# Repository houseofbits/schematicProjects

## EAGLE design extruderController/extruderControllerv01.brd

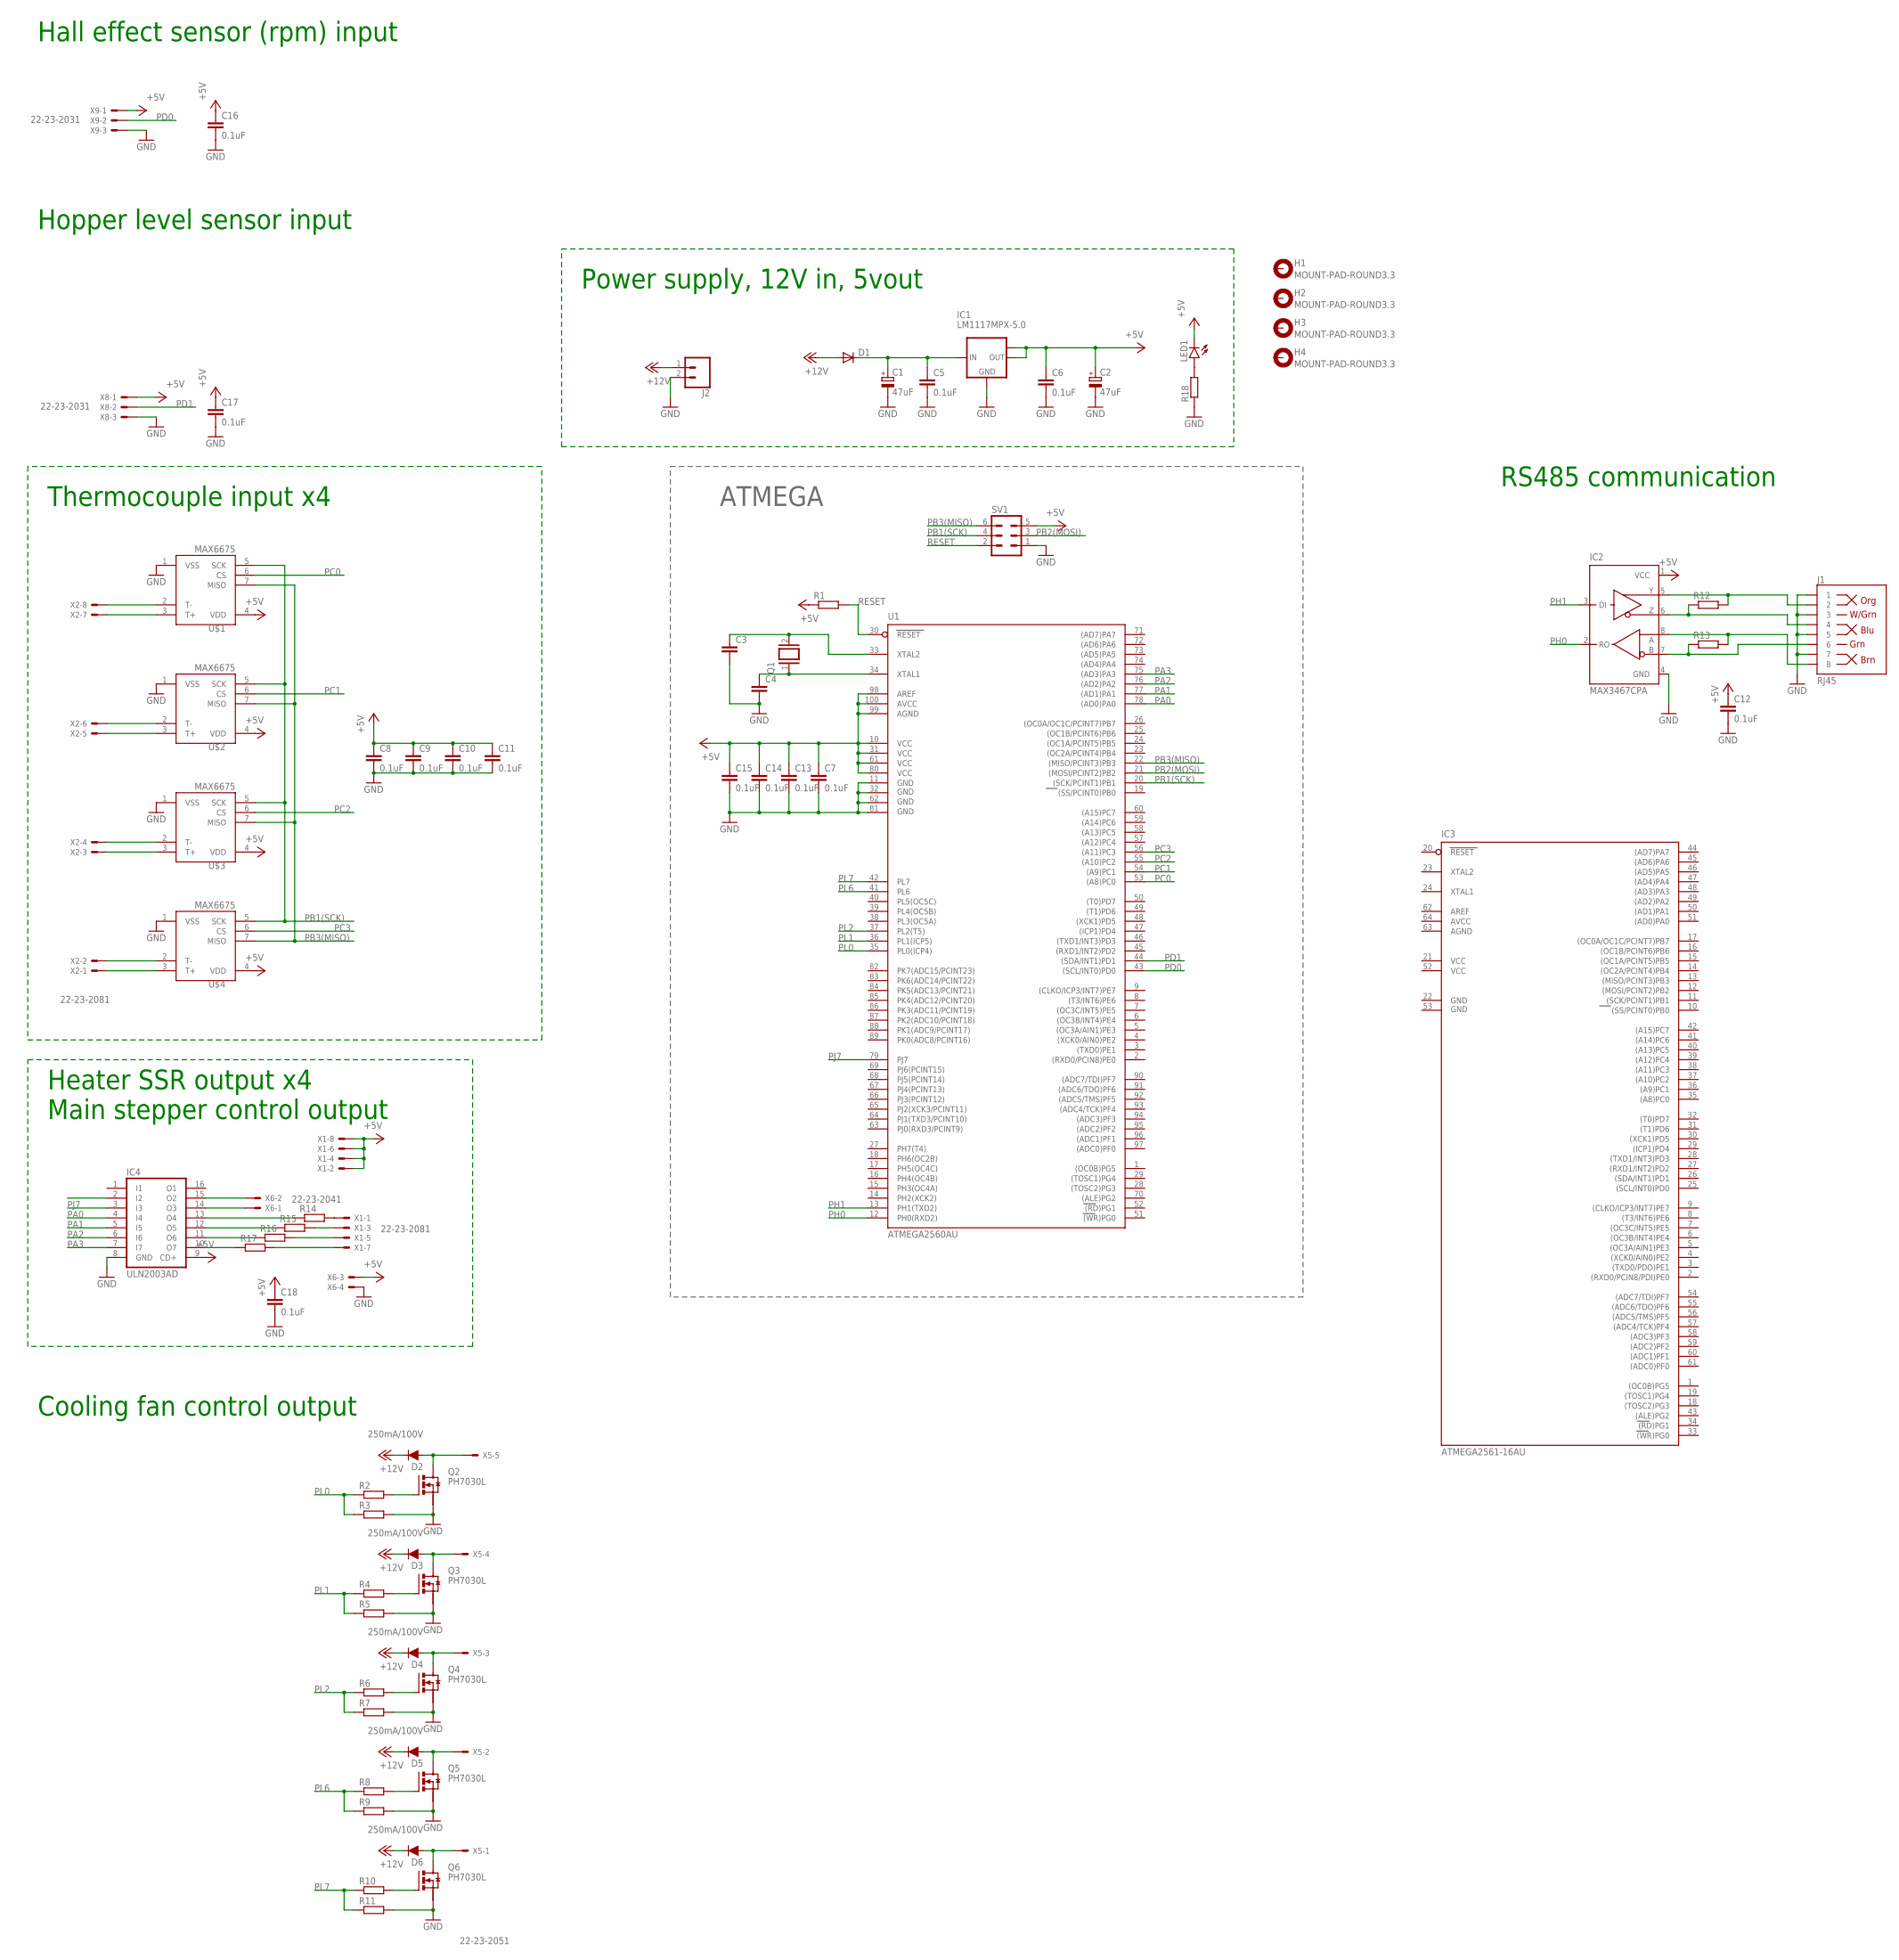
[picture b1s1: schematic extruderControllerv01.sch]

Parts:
C1, C2: 47uF; PANASONIC_D
C3, C4: C-EUC0603; C0603
C5, C6, C7, C8, C9, C10, C11, C12, C13, C14, C15, C16, C17, C18: 0.1uF; C0603
D1: DIODE-SMB; SMB
D2, D3, D4, D5, D6: 250mA/100V; SOD-323
H1, H2, H3, H4: MOUNT-PAD-ROUND3.3; 3,3-PAD
IC1: LM1117MPX-5.0; SOT223
IC2: MAX3467CPA; SO08
IC3: ATMEGA2561-16AU; TQFP64
IC4: ULN2003AD; SO16
J1: RJ45; RJ45-8
J2: CONN_023.5MM; SCREWTERMINAL-3.5MM-2
LED1: LEDSML1206; SML1206
Q1: XTAL/S; QS
Q2, Q3, Q4, Q5, Q6: PH7030L; SOT669
R1, R2, R3, R4, R5, R6, R7, R8, R9, R10, R11, R14, R15, R16, R17, R18: R-EU_R0805; R0805
R12, R13: R-EU_R1210; R1210
SV1: MA03-2
U1: ATMEGA2560AU; TQFP100
U$1, U$2, U$3, U$4: MAX6675; SO08-MAX6675
X1, X2: 22-23-2081
X5: 22-23-2051
X6: 22-23-2041
X8, X9: 22-23-2031

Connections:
+5V: C2.+, C6.1, C7.1, C8.1, C9.1, C10.1, C11.1, C12.1, C13.1, C14.1, C15.1, C16.1, C17.1, C18.1, IC1.2 (OUT), IC1.TAB (OUT1), IC2.1 (VCC), IC4.9 (CD+), LED1.C, R1.1, SV1.5, U1.10 (VCC), U1.31 (VCC1), U1.61 (VCC2), U1.80 (VCC3), U1.98 (AREF), U1.99 (AGND), U1.100 (AVCC), U$1.4 (VDD), U$2.4 (VDD), U$3.4 (VDD), U$4.4 (VDD), X1.2, X1.4, X1.6, X1.8, X6.3, X8.1, X9.1
+12V: D1.A, D2.C, D3.C, D4.C, D5.C, D6.C, J2.1
AGND: IC3.63 (AGND)
AVCC: IC3.64 (AVCC)
GND: C1.-, C2.-, C3.2, C4.2, C5.2, C6.2, C7.2, C8.2, C9.2, C10.2, C11.2, C12.2, C13.2, C14.2, C15.2, C16.2, C17.2, C18.2, IC1.1 (GND), IC2.4 (GND), IC3.22 (GND), IC4.8 (GND), J1.1, J1.3, J1.5, J1.7, J2.2, Q2.1 (S), Q3.1 (S), Q4.1 (S), Q5.1 (S), Q6.1 (S), R3.2, R5.2, R7.2, R9.2, R11.2, R18.1, SV1.1, U1.11 (GND), U1.32 (GND1), U1.62 (GND2), U1.81 (GND3), U$1.1 (VSS), U$2.1 (VSS), U$3.1 (VSS), U$4.1 (VSS), X6.4, X8.3, X9.3
GND1: IC3.53 (GND1)
unnamed: Q2.4 (G), R2.2
unnamed: R14.2, X1.1
unnamed: U$1.2 (T-), X2.8
unnamed: U$1.3 (T+), X2.7
unnamed: U$2.2 (T-), X2.6
unnamed: U$2.3 (T+), X2.5
unnamed: U$3.2 (T-), X2.4
unnamed: U$3.3 (T+), X2.3
unnamed: U$4.2 (T-), X2.2
unnamed: U$4.3 (T+), X2.1
unnamed: R15.2, X1.3
unnamed: R16.2, X1.5
unnamed: R17.2, X1.7
unnamed: C1.+, C5.1, D1.C, IC1.3 (IN)
unnamed: C3.1, Q1.2, U1.33 (XTAL2)
unnamed: C4.1, Q1.1, U1.34 (XTAL1)
unnamed: IC4.14 (O3), X6.1
unnamed: D2.A, Q2.MB (D), X5.5
unnamed: Q3.4 (G), R4.2
unnamed: IC4.15 (O2), X6.2
unnamed: D3.A, Q3.MB (D), X5.4
unnamed: Q4.4 (G), R6.2
unnamed: IC2.7 (B), J1.6, R13.1
unnamed: D4.A, Q4.MB (D), X5.3
unnamed: Q5.4 (G), R8.2
unnamed: IC4.13 (O4), R14.1
unnamed: D5.A, Q5.MB (D), X5.2
unnamed: Q6.4 (G), R10.2
unnamed: IC2.6 (Z), J1.4, R12.1
unnamed: D6.A, Q6.MB (D), X5.1
unnamed: IC2.5 (Y), J1.2, R12.2
unnamed: IC2.8 (A), J1.8, R13.2
unnamed: IC4.12 (O5), R15.1
unnamed: IC4.11 (O6), R16.1
unnamed: IC4.10 (O7), R17.1
unnamed: LED1.A, R18.2
PA0: IC4.4 (I4), U1.78 ((AD0)PA0)
PA1: IC4.5 (I5), U1.77 ((AD1)PA1)
PA2: IC4.6 (I6), U1.76 ((AD2)PA2)
PA3: IC4.7 (I7), U1.75 ((AD3)PA3)
PB1(SCK): SV1.4, U1.20 ((SCK/PCINT1)PB1), U$1.5 (SCK), U$2.5 (SCK), U$3.5 (SCK), U$4.5 (SCK)
PB2(MOSI): SV1.3, U1.21 ((MOSI/PCINT2)PB2)
PB3(MISO): SV1.6, U1.22 ((MISO/PCINT3)PB3), U$1.7 (MISO), U$2.7 (MISO), U$3.7 (MISO), U$4.7 (MISO)
PC0: U1.53 ((A8)PC0), U$1.6 (CS)
PC1: U1.54 ((A9)PC1), U$2.6 (CS)
PC2: U1.55 ((A10)PC2), U$3.6 (CS)
PC3: U1.56 ((A11)PC3), U$4.6 (CS)
PD0: U1.43 ((SCL/INT0)PD0), X9.2
PD1: U1.44 ((SDA/INT1)PD1), X8.2
PH0: IC2.2 (RO), U1.12 (PH0(RXD2))
PH1: IC2.3 (DI), U1.13 (PH1(TXD2))
PJ7: IC4.3 (I3), U1.79 (PJ7)
PL0: R2.1, R3.1, U1.35 (PL0(ICP4))
PL1: R4.1, R5.1, U1.36 (PL1(ICP5))
PL2: R6.1, R7.1, U1.37 (PL2(T5))
PL6: R8.1, R9.1, U1.41 (PL6)
PL7: R10.1, R11.1, U1.42 (PL7)
RESET: R1.2, SV1.2, U1.30 (RESET)
VCC: IC3.21 (VCC)
VCC1: IC3.52 (VCC1)

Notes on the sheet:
Power supply, 12V in, 5vout
ATMEGA
Thermocouple input x4
Heater SSR output x4
Main stepper control output
Hall effect sensor (rpm) input
RS485 communication
Hopper level sensor input
Cooling fan control output

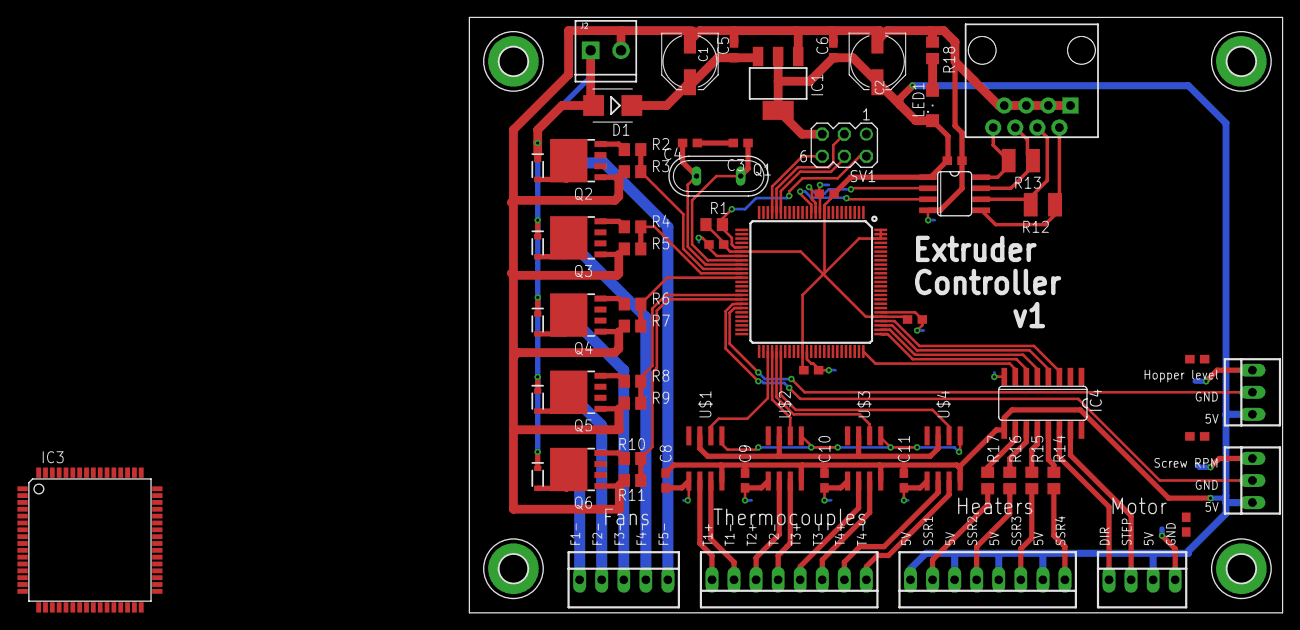
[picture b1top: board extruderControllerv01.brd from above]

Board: 2 copper layers, 93.7 x 68.6 mm, 71 parts (0 on the bottom side), 61 nets.

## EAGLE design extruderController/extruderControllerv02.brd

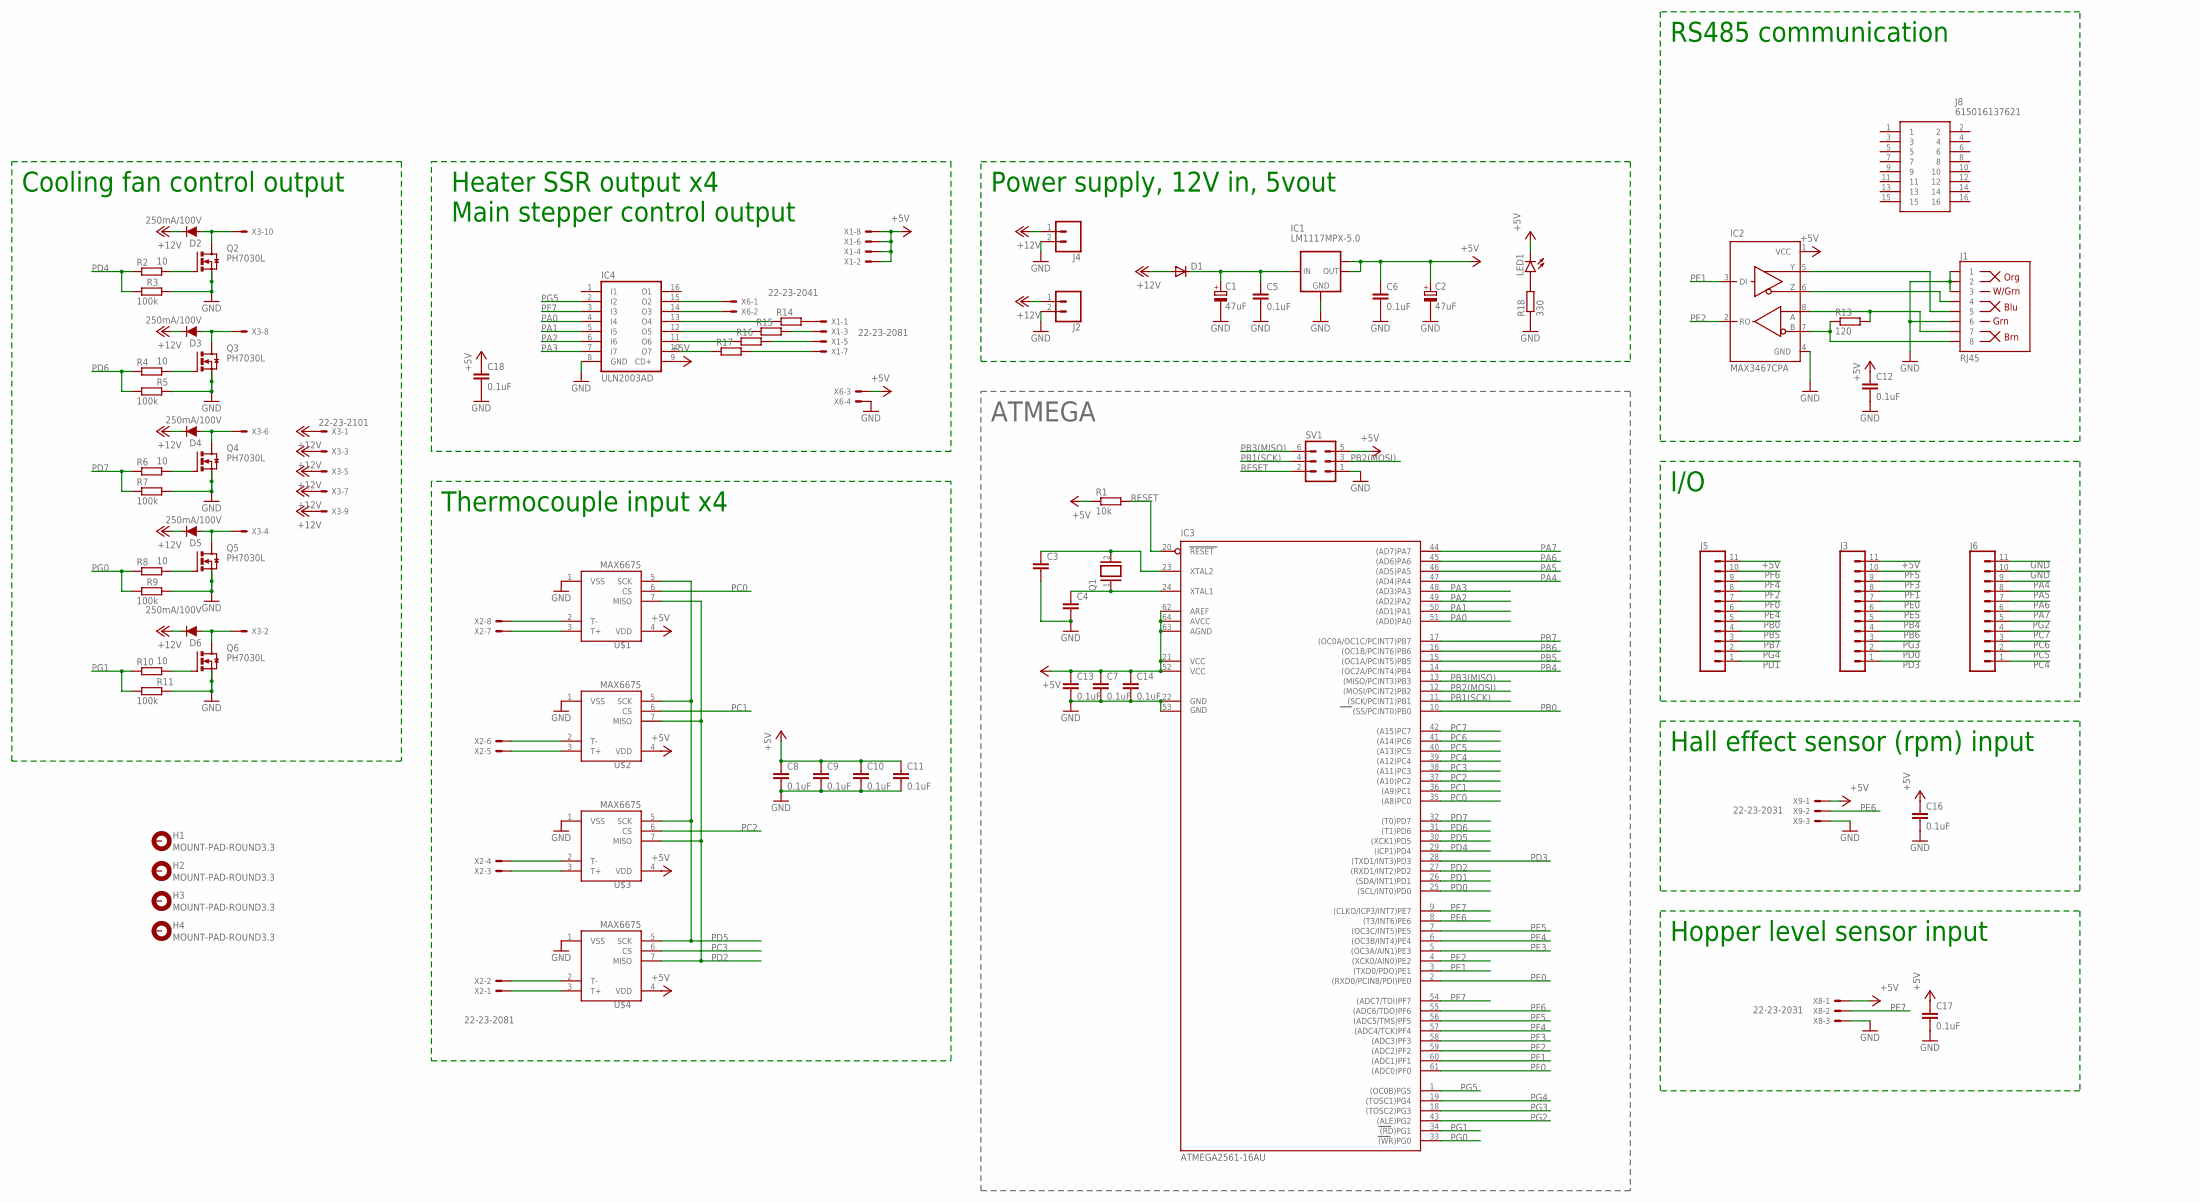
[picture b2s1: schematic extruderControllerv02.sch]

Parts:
C1, C2: 47uF; PANASONIC_D
C3, C4: C-EUC0603; C0603
C5, C6, C7, C8, C9, C10, C11, C12, C13, C14, C16, C17, C18: 0.1uF; C0603
D1: DIODE-SMB; SMB
D2, D3, D4, D5, D6: 250mA/100V; SOD-323
H1, H2, H3, H4: MOUNT-PAD-ROUND3.3; 3,3-PAD
IC1: LM1117MPX-5.0; SOT223
IC2: MAX3467CPA; SO08
IC3: ATMEGA2561-16AU; TQFP64
IC4: ULN2003AD; SO16
J1: RJ45; RJ45-8
J2, J4: CONN_023.5MM; SCREWTERMINAL-3.5MM-2
J3, J5, J6: CONN_11; 1X11
J8: 615016137621; WR-MJ
LED1: LEDSML1206; SML1206
Q1: XTAL/S; QS
Q2, Q3, Q4, Q5, Q6: PH7030L; SOT669
R1: 10k; R0805
R2, R4, R6, R8, R10: 10; R0805
R3, R5, R7, R9, R11: 100k; R0805
R13: 120; R1210
R14, R15, R16, R17: R-EU_R0805; R0805
R18: 330; R0805
SV1: MA03-2
U$1, U$2, U$3, U$4: MAX6675; SO08-MAX6675
X1, X2: 22-23-2081
X3: 22-23-2101
X6: 22-23-2041
X8, X9: 22-23-2031

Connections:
+5V: C2.+, C6.1, C7.1, C8.1, C9.1, C10.1, C11.1, C12.1, C13.1, C14.1, C16.1, C17.1, C18.1, IC1.2 (OUT), IC1.TAB (OUT1), IC2.1 (VCC), IC3.21 (VCC), IC3.52 (VCC1), IC3.62 (AREF), IC3.63 (AGND), IC3.64 (AVCC), IC4.9 (CD+), J3.11, J5.11, LED1.C, R1.1, SV1.5, U$1.4 (VDD), U$2.4 (VDD), U$3.4 (VDD), U$4.4 (VDD), X1.2, X1.4, X1.6, X1.8, X6.3, X8.1, X9.1
+12V: D1.A, D2.C, D3.C, D4.C, D5.C, D6.C, J2.1, J4.1, X3.1, X3.3, X3.5, X3.7, X3.9
GND: C1.-, C2.-, C3.2, C4.2, C5.2, C6.2, C7.2, C8.2, C9.2, C10.2, C11.2, C12.2, C13.2, C14.2, C16.2, C17.2, C18.2, IC1.1 (GND), IC2.4 (GND), IC3.22 (GND), IC3.53 (GND1), IC4.8 (GND), J1.1, J1.2, J1.3, J1.6, J2.2, J4.2, J6.10, J6.11, Q2.1 (S), Q2.2 (S), Q2.3 (S), Q3.1 (S), Q3.2 (S), Q3.3 (S), Q4.1 (S), Q4.2 (S), Q4.3 (S), Q5.1 (S), Q5.2 (S), Q5.3 (S), Q6.1 (S), Q6.2 (S), Q6.3 (S), R3.2, R5.2, R7.2, R9.2, R11.2, R18.1, SV1.1, U$1.1 (VSS), U$2.1 (VSS), U$3.1 (VSS), U$4.1 (VSS), X6.4, X8.3, X9.3
unnamed: Q2.4 (G), R2.2
unnamed: R14.2, X1.1
unnamed: U$1.2 (T-), X2.8
unnamed: U$1.3 (T+), X2.7
unnamed: U$2.2 (T-), X2.6
unnamed: U$2.3 (T+), X2.5
unnamed: U$3.2 (T-), X2.4
unnamed: U$3.3 (T+), X2.3
unnamed: U$4.2 (T-), X2.2
unnamed: U$4.3 (T+), X2.1
unnamed: R15.2, X1.3
unnamed: R16.2, X1.5
unnamed: R17.2, X1.7
unnamed: IC4.15 (O2), X6.1
unnamed: C1.+, C5.1, D1.C, IC1.3 (IN)
unnamed: C3.1, IC3.23 (XTAL2), Q1.2
unnamed: C4.1, IC3.24 (XTAL1), Q1.1
unnamed: IC4.14 (O3), X6.2
unnamed: D2.A, Q2.MB (D), X3.10
unnamed: Q3.4 (G), R4.2
unnamed: D3.A, Q3.MB (D), X3.8
unnamed: Q4.4 (G), R6.2
unnamed: IC2.7 (B), J1.8, R13.1
unnamed: D4.A, Q4.MB (D), X3.6
unnamed: Q5.4 (G), R8.2
unnamed: IC4.13 (O4), R14.1
unnamed: D5.A, Q5.MB (D), X3.4
unnamed: Q6.4 (G), R10.2
unnamed: IC2.5 (Y), J1.5
unnamed: D6.A, Q6.MB (D), X3.2
unnamed: IC2.8 (A), J1.7, R13.2
unnamed: IC4.12 (O5), R15.1
unnamed: IC4.11 (O6), R16.1
unnamed: IC4.10 (O7), R17.1
unnamed: LED1.A, R18.2
unnamed: IC2.6 (Z), J1.4
PA0: IC3.51 ((AD0)PA0), IC4.4 (I4)
PA1: IC3.50 ((AD1)PA1), IC4.5 (I5)
PA2: IC3.49 ((AD2)PA2), IC4.6 (I6)
PA3: IC3.48 ((AD3)PA3), IC4.7 (I7)
PA4: IC3.47 ((AD4)PA4), J6.9
PA5: IC3.46 ((AD5)PA5), J6.8
PA6: IC3.45 ((AD6)PA6), J6.7
PA7: IC3.44 ((AD7)PA7), J6.6
PB0: IC3.10 ((SS/PCINT0)PB0), J5.5
PB1(SCK): IC3.11 ((SCK/PCINT1)PB1), SV1.4
PB2(MOSI): IC3.12 ((MOSI/PCINT2)PB2), SV1.3
PB3(MISO): IC3.13 ((MISO/PCINT3)PB3), SV1.6
PB4: IC3.14 ((OC2A/PCINT4)PB4), J3.5
PB5: IC3.15 ((OC1A/PCINT5)PB5), J5.4
PB6: IC3.16 ((OC1B/PCINT6)PB6), J3.4
PB7: IC3.17 ((OC0A/OC1C/PCINT7)PB7), J5.3
PC0: IC3.35 ((A8)PC0), U$1.6 (CS)
PC1: IC3.36 ((A9)PC1), U$2.6 (CS)
PC2: IC3.37 ((A10)PC2), U$3.6 (CS)
PC3: IC3.38 ((A11)PC3), U$4.6 (CS)
PC4: IC3.39 ((A12)PC4), J6.1
PC5: IC3.40 ((A13)PC5), J6.2
PC6: IC3.41 ((A14)PC6), J6.3
PC7: IC3.42 ((A15)PC7), J6.4
PD0: IC3.25 ((SCL/INT0)PD0), J3.2
PD1: IC3.26 ((SDA/INT1)PD1), J5.1
PD2: IC3.27 ((RXD1/INT2)PD2), U$1.7 (MISO), U$2.7 (MISO), U$3.7 (MISO), U$4.7 (MISO)
PD3: IC3.28 ((TXD1/INT3)PD3), J3.1
PD4: IC3.29 ((ICP1)PD4), R2.1, R3.1
PD5: IC3.30 ((XCK1)PD5), U$1.5 (SCK), U$2.5 (SCK), U$3.5 (SCK), U$4.5 (SCK)
PD6: IC3.31 ((T1)PD6), R4.1, R5.1
PD7: IC3.32 ((T0)PD7), R6.1, R7.1
PE0: IC3.2 ((RXD0/PCIN8/PDI)PE0), J3.7
PE1: IC2.3 (DI), IC3.3 ((TXD0/PDO)PE1)
PE2: IC2.2 (RO), IC3.4 ((XCK0/AIN0)PE2)
PE3: IC3.5 ((OC3A/AIN1)PE3)
PE4: IC3.6 ((OC3B/INT4)PE4), J5.6
PE5: IC3.7 ((OC3C/INT5)PE5), J3.6
PE6: IC3.8 ((T3/INT6)PE6), X9.2
PE7: IC3.9 ((CLKO/ICP3/INT7)PE7), X8.2
PF0: IC3.61 ((ADC0)PF0), J5.7
PF1: IC3.60 ((ADC1)PF1), J3.8
PF2: IC3.59 ((ADC2)PF2), J5.8
PF3: IC3.58 ((ADC3)PF3), J3.9
PF4: IC3.57 ((ADC4/TCK)PF4), J5.9
PF5: IC3.56 ((ADC5/TMS)PF5), J3.10
PF6: IC3.55 ((ADC6/TDO)PF6), J5.10
PF7: IC3.54 ((ADC7/TDI)PF7), IC4.3 (I3)
PG0: IC3.33 ((WR)PG0), R8.1, R9.1
PG1: IC3.34 ((RD)PG1), R10.1, R11.1
PG2: IC3.43 ((ALE)PG2), J6.5
PG3: IC3.18 ((TOSC2)PG3), J3.3
PG4: IC3.19 ((TOSC1)PG4), J5.2
PG5: IC3.1 ((OC0B)PG5), IC4.2 (I2)
RESET: IC3.20 (RESET), R1.2, SV1.2

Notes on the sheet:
Power supply, 12V in, 5vout
ATMEGA
Thermocouple input x4
Heater SSR output x4
Main stepper control output
Hall effect sensor (rpm) input
RS485 communication
Hopper level sensor input
Cooling fan control output
I/O

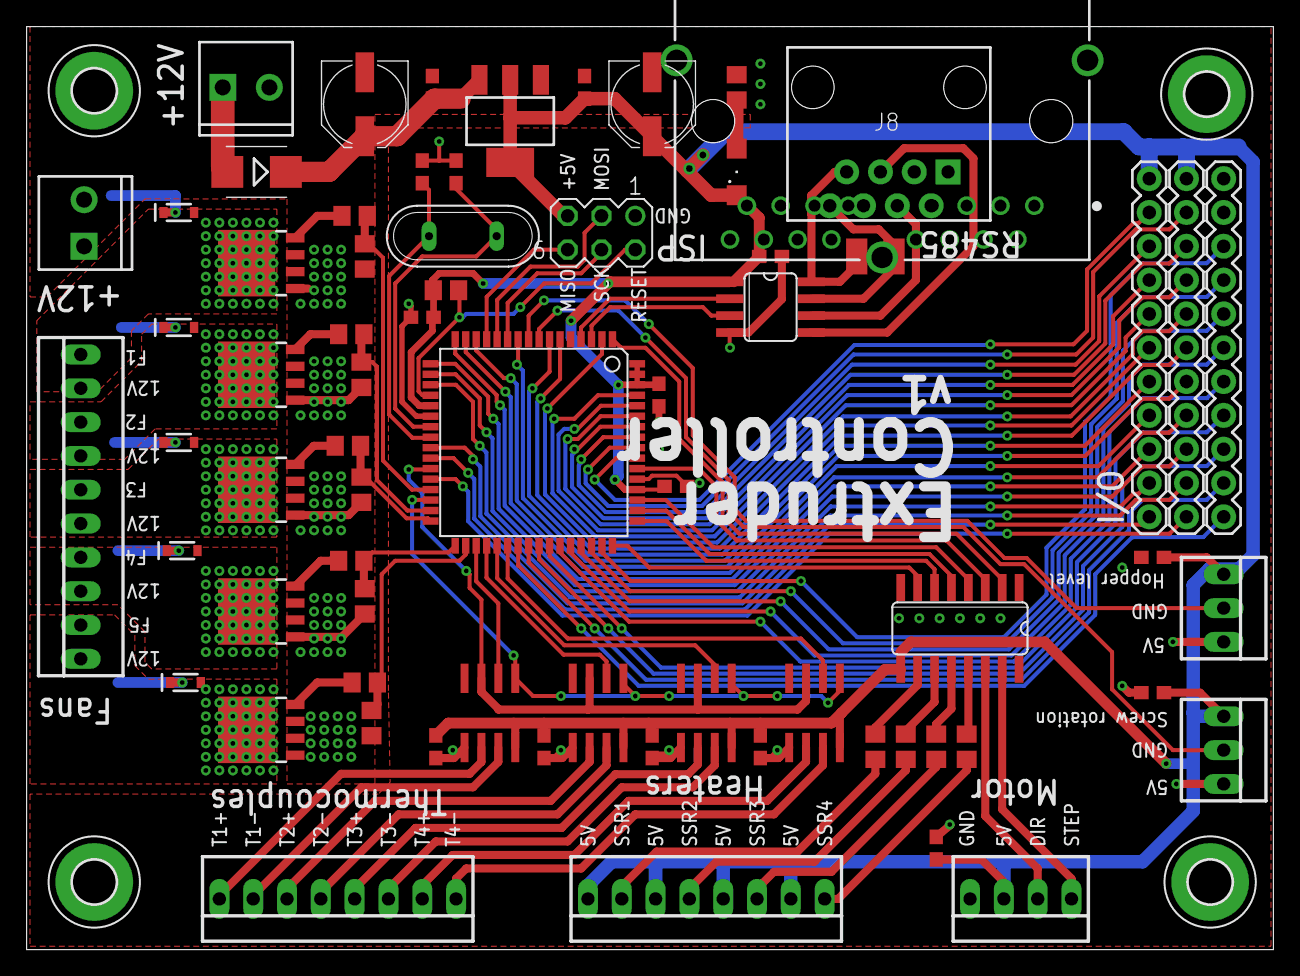
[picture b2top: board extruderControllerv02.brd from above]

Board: 2 copper layers, 93.7 x 69.3 mm, 73 parts (0 on the bottom side), 93 nets.

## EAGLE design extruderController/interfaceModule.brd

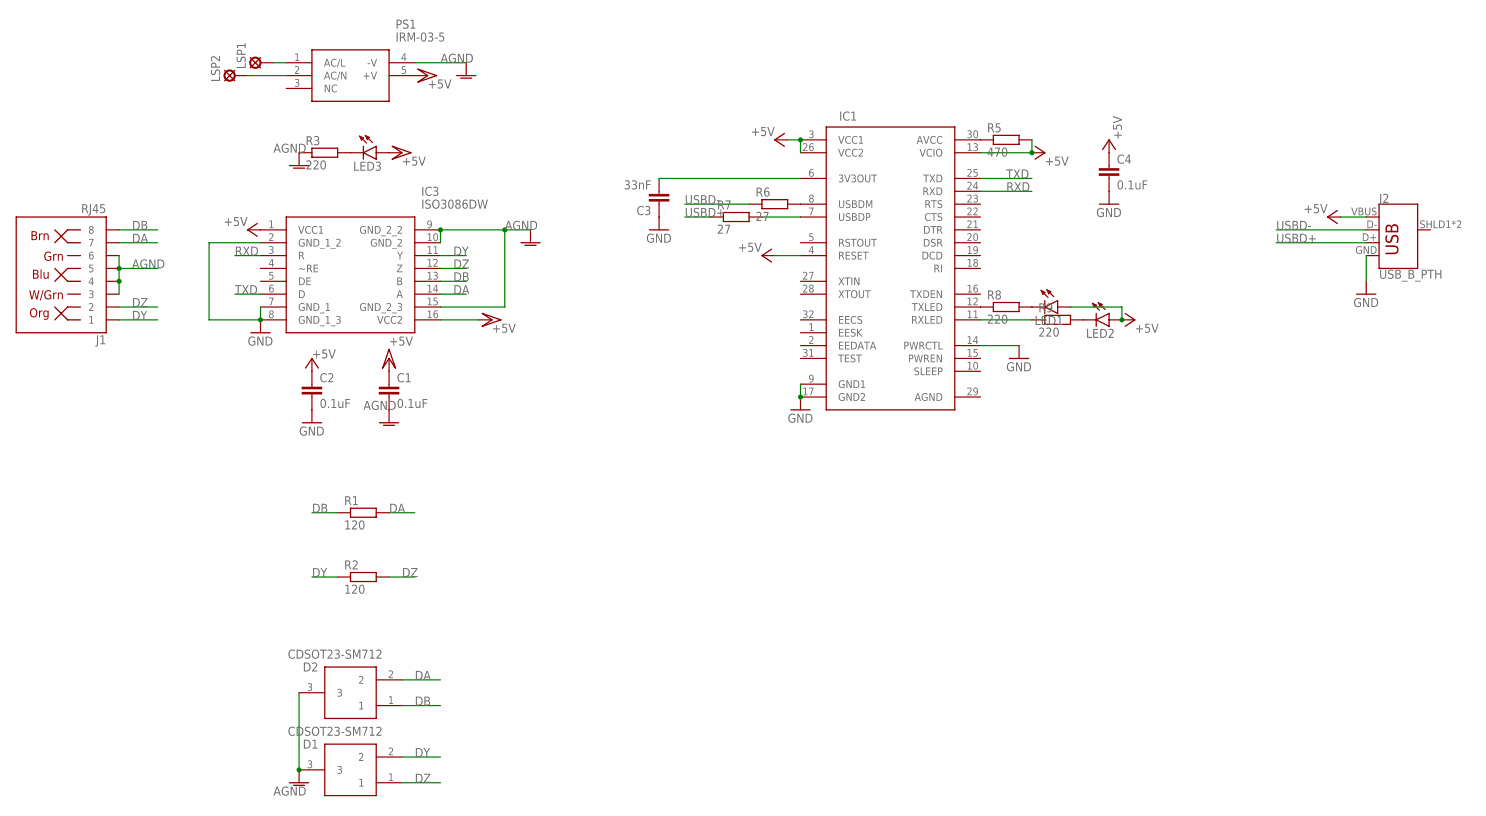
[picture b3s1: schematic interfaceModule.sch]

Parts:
C1, C2, C4: 0.1uF; C0603
C3: 33nF; C0603
D1, D2: CDSOT23-SM712; SOT95P230X117-3N
IC1: FT232BM; QFP-32
IC3: ISO3086DW; SOIC127P1030X265-16N
J1: RJ45; RJ45-8
J2: USB_B_PTH; USB-B-PTH
LED1, LED2, LED3: LEDSML1206; SML1206
LSP1, LSP2: SE14
PS1: IRM-03-5; IRM0312
R1, R2: 120; R1210
R3, R8, R9: 220; R0805
R5: 470; R0805
R6, R7: 27; R0805

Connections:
+5V: C2.1, C4.1, IC1.3 (VCC1), IC1.4 (RESET), IC1.13 (VCIO), IC1.26 (VCC2), IC3.1 (VCC1), J2.VBUS, LED1.A, LED2.A, R5.2
AGND: C1.2, D1.3, D2.3, IC3.9 (GND_2_2), IC3.10 (GND_2), IC3.15 (GND_2_3), J1.3, J1.4, J1.5, J1.6, PS1.4 (-V), R3.1
DA: D2.2, IC3.14 (A), J1.7, R1.2
DB: D2.1, IC3.13 (B), J1.8, R1.1
DY: D1.2, IC3.11 (Y), J1.1, R2.1
DZ: D1.1, IC3.12 (Z), J1.2, R2.2
GND: C2.2, C3.1, C4.2, IC1.9 (GND1), IC1.14 (PWRCTL), IC1.17 (GND2), IC3.2 (GND_1_2), IC3.7 (GND_1), IC3.8 (GND_1_3), J2.GND
unnamed: LSP1.MP, PS1.1 (AC/L)
unnamed: LSP2.MP, PS1.2 (AC/N)
unnamed: IC1.8 (USBDM), R6.2
unnamed: IC1.30 (AVCC), R5.1
unnamed: IC1.7 (USBDP), R7.2
unnamed: C3.2, IC1.6 (3V3OUT)
unnamed: IC1.12 (TXLED), R8.1
unnamed: IC1.11 (RXLED), R9.1
unnamed: LED2.C, R9.2
unnamed: LED1.C, R8.2
unnamed: LED3.C, R3.2
RXD: IC1.24 (RXD), IC3.3 (R)
TXD: IC1.25 (TXD), IC3.6 (D)
USBD+: J2.D+, R7.1
USBD-: J2.D-, R6.1
VCC/2: C1.1, IC3.16 (VCC2), LED3.A, PS1.5 (+V)

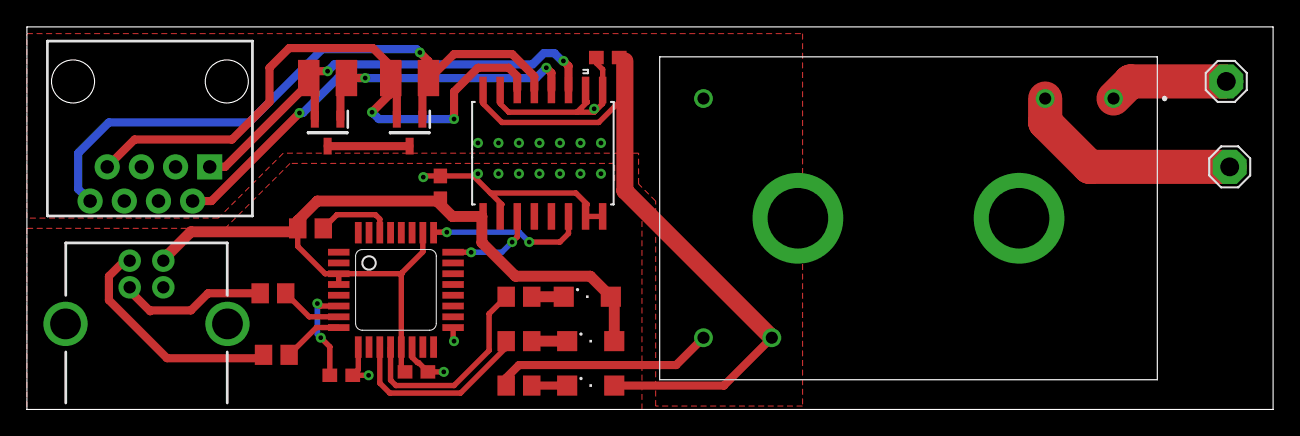
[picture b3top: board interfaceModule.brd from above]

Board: 2 copper layers, 92.6 x 28.4 mm, 24 parts (0 on the bottom side), 23 nets.

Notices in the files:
parts and their libraries:
SparkFun-AnalogIC: Licensing:Creative Commons ShareAlike 4.0 International - https://creativecommons.org/licenses/by-sa/4.0
FTDI: FTDI USB-serial converters and FIFOs, © UNITRONIC AG
